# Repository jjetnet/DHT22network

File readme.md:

# DHT22network
wifi dht22 network

Note: there are many similar, and probably better implementation of
similar concepts. My python coding in particular is far from optimal
or elegant. This implementation has mobile notifications, plots and water partial pressure
calculations which distinguishes it from others, but if you don't need
this look around for better implementations.

## Overview:

Arduino code, eagle files and python script for a wifi based array of
humidity and temperature sensors sending data back periodically to a
server. The server generates plots and tables of current data
displayed on a webpage - on the local server, and/or on a remote web
server through ftp. The sensors are meant for indoors reading, with
outside temperature read from publicly available data from the
Australian bureau of meteorology (data for australia only...).  The
number of sensors is not really limited (Although past a certain
number i'm sure bugs will emerge), and the server just adapts when a
new sensor comes online.

Each sensor can be battery operated for a number of months or even
years depending on refresh settings and battery - power consumption
between readings is minimal. The server can send notificatinos to
android and iphone phones using the free pushetta service/app (See
www.pushetta.com) when outside temperature goes above or below user
defined thresholds - useful to remember to close windows, curtains or
blinds.  Each sensor also reads its battery level, also displayed on
the webpage as battery voltage with a crude red/green color coding
depending on battery state.

For example of what the webpage looks like see
webpageexample.png. Data displayed includes temperature, relative
humidity and the water partial pressure - the latter is absolute
rather than relative, and is more informative if you want to control
the flow of humidity between two rooms or between outdoows and
indoors: if two rooms are at different temperatures but identical
relative humidity, there will still be a net flow of water vapour from
the space with the higher partial water pressure to the room with the
lower one. If you want to keep humidity down indoors in summer, this
is the quantity to watch to close/open windows, rather than the
relative humidity.

Each sensor is based on an esp8266 - specifically i used a sparkfun
esp8266 thing, which includes a convenient LiPo battery charger. Wifi
network and key, location name, and python server addess and port have
to be adjusted in the arduino code before uploading.

The server collecting data is a python script, which has to be run
with sufficient priviledges to write onto the web server's folder (eg
`/var/www/` ). All server data is defined in a separate configuration
script (tempTCPconfig.py). I run mine on a raspbery pi.

## Hardware

A minimal version can be assembled without PCB, using a ESP8266 thing the DHT22 sensor, and a jumper wire between XPD and DTR (which needs to be removed for programming). To add battery monitoring, two resistors straight onto the ESP8266 thing between Vin, Gnd and Analog in forming a ~1/5 voltage divider is enough. (220k between Vin and Analog in, 56k between gnd and Analog in) (see eagle schematic for details).

Alternatively, a PCB can be used to clean up the circuit: 

The current version of the pcb (eagle file) is awkward - components are on
the copper side, which makes for some difficult soldering for some
pins.

The two jpeg files show an example of an assembled sensor module using PCB,
outside its casing - as mentioned it is a tad awkward in this
implementation. There's some hot glue that was requried to stabilise
some of the copper wiring which had lifted off when accidentally
pushing on the module... The top view with sensor rotated shows the
two resistors that make up the voltage divider to bring the battery
voltage within the range of the ESP8266 1V ADC, as well as the jumper
that needs to be removed for programming (it connects XPD to DTR to
enable deep sleep - see [sparkfun's sleepmode tutorial](https://learn.sparkfun.com/tutorials/esp8266-thing-hookup-guide/example-sketch-goodnight-thing-sleep-mode). The
six open pins are a copy of the programming port of the esp8266 so
that the the module can still be programmed.  This particular example
uses a DHT22 module from df robotics, but a naked DHT22 can also be
used.

For the battery to last months rather than hours or days, the power LED has to be disconnected, see [sparkfun's sleepmode tutorial](https://learn.sparkfun.com/tutorials/esp8266-thing-hookup-guide/example-sketch-goodnight-thing-sleep-mode)

For this example, I used a LiPo 1000mAh LiPo battery, which is of similar size to the esp8266 thing module.

## Installation:
The python-based server requires a number of libraries,
some of which are not in the default python install for raspberry
pi (if you chose to run the server on a raspberry pi). In particular pushetta, matplotlib and a recent version of numpy
are requried, which you may have to install from source depending on
your distribution/package manager. I'm not sure which version is
required, but it runs with numpy 1.11.0, matplotlib 1.1.1rc2, pushetta
1.0.15.
Notifications require a free account with the pushetta service. For this, and how to install the pushetta python package, see [the puhsetta help page](http://pushetta.com/pushetta-docs).
Feel free to contact me (open an issue) if you have any trouble installing or running the server.

## Updates:
### 13/08/16
* increased stability: exception handling for ftp and pushetta. The python server seems very stable now.
* remover redundant, unused plot routine.

### 30/07/16
* fixed stability issues when remote ftp server or bureau of meteorology websites are not responsive.
* fixed plotting - no more error messages when insufficient data points, and limited long-term plot to last 30 days for readability

## Known issues:
* Arduino code:  If the server is down or a sensor module fails for any other reason to communicate with the server, it will keep trying continuously for ever - the battery will then run out rapidly.
* safety: ftp passwords are in clear text in the python configuration file, and  so is the wifi password in the arduino code. MAke sure to protect those files. TCP communications between sensor module and server are unencrypted.

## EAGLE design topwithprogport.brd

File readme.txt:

# DHT22network
wifi dht22 network

Note: there are many similar, and probably better implementation of similar concepts. My python coding in particular is far from optimal or elegant. Look around for better implementations...

*** Overview: ***

Arduino code, eagle files and python script for a wifi based array of  humidity and temperature sensors sending data back periodcially to a server. The server generates plots and tables of current data displayed  on a webpage - on the local server, and/or on a remote web server through ftp. The sensors are meant for indoors reading, with outside temperature read from publicly available data from the Australian bureau of meteorology (data for australia only...).
The number of sensors is not really limited (Although past a certain number i'm sure bugs will emerge), and the server just adapts when a new sensor comes online. 

Each sensor can be battery operated for a number of months or even years depending on refresh settings and battery  - power consumption between readings is minimal. The server can send notificatinos to android and iphone phones using the free pushetta service/app (See www.pushetta.com) when outside temperature goes above or below user defined  thresholds - useful to remember to close windows, curtains or blinds.
Each sensor also reads its battery level, also displayed on the webpage as battery voltage with a crude red/green color coding depending on battery state.

For example of what the webpage looks like see webpageexample.png. Data displayed includes temperature, relative humidity and the water partial pressure - the latter is absolute rather than relative, and is more informative if you want to control the flow of humidity between two rooms or between outdoows and indoors: if two roowms are at different temperatures but identical relative humidity, there will still be a net flow of water vapour from the space with the higher partial water pressure to the room with the lower one. If you want to keep humidity down indoors in summer, this is the quantity to watch to close/open windows, rather than the relative humidity.

Each sensor is based on an esp8266 - specifically i used a sparkfun esp8266 thing, which includes a convenient LiPo battery charger. Wifi network and key,  location name, and python server addess and port have to be adjusted in the arduino code before uploading. 

The server collecting data is a python script, which has to be run with sufficient priviledges to write onto the web server's  folder (eg /var/www/ ). All server data is defined in a separate configuration script (tempTCPconfig.py). I run mine on a raspbery pi.

*** Hardware ***

The current version of eagle file's pcb is awkward - components are on the copper side, which makes for some difficult soldering for some pins. 

The two jpeg files show an example of an assembled sensor module, outside its casing - as mentioned it is a tad awkward in this implementation. There's some hot glue that was requried to stabilise some of the copper wiring which had lifted off when accidentally pushing on the module... The top view with sensor rotated shows the two resistors that make up the voltage divider to bring the battery voltage within the range of the ESP8266 1V ADC, as well as the jumper that needs to be removed for programming (it connects XPD to DTR to enable  deep sleep - see https://learn.sparkfun.com/tutorials/esp8266-thing-hookup-guide/example-sketch-goodnight-thing-sleep-mode). The six open pins are a copy of the programming port of the esp8266 so that the the module can still be programmed.
This particular example uses a DHT22 module from df robotics, but a naked DHT22 can also be used.

For the battery to last months rather than hours or days, the power LED has to be disconnected, see https://learn.sparkfun.com/tutorials/esp8266-thing-hookup-guide/example-sketch-goodnight-thing-sleep-mode

For this example, I used a LiPo 1000mAh LiPo battery, which is of similar size to the esp8266 thing module.

Known issues:
- Arduino code:  If the server is down or a sensor module fails for any other reason to communicate with the server, it will keep trying continuously for ever - the battery will then run out rapidly.
- Python code: the server is not bug free. It is stable for days to weeks at a time, but occasionally stops if communications with sensor module isn't quite as expected. I may now have fixed this bug - but i won't be sure for another few weeks...
- safety: ftp passwords are in clear text in the python configuration file, and  so is the wifi password in the arduino code. MAke sure to protect those files...

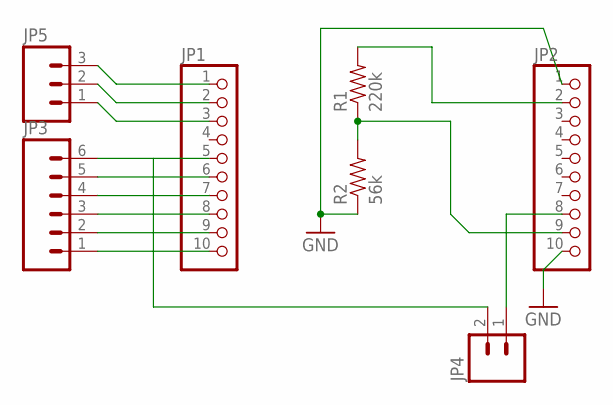
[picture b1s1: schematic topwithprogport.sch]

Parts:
JP1, JP2: PINHD-1X10; 1X10
JP3: M06LONGPADS; 1X06_LONGPADS
JP4: M02LOCK_LONGPADS; 1X02_LOCK_LONGPADS
JP5: M03LOCK_LONGPADS; 1X03_LOCK_LONGPADS
R1: 220k; AXIAL-0.4
R2: 56k; AXIAL-0.4

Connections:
GND: JP1.1, JP2.1, JP2.10, JP5.3, R2.P$1 (1)
unnamed: JP2.9, R1.P$1 (1), R2.P$2 (2)
unnamed: JP2.2, R1.P$2 (2)
unnamed: JP2.8, JP4.1
unnamed: JP1.5, JP3.6, JP4.2
unnamed: JP1.6, JP3.5
unnamed: JP1.7, JP3.4
unnamed: JP1.8, JP3.3
unnamed: JP1.9, JP3.2
unnamed: JP1.10, JP3.1
unnamed: JP1.2, JP5.2
unnamed: JP1.3, JP5.1

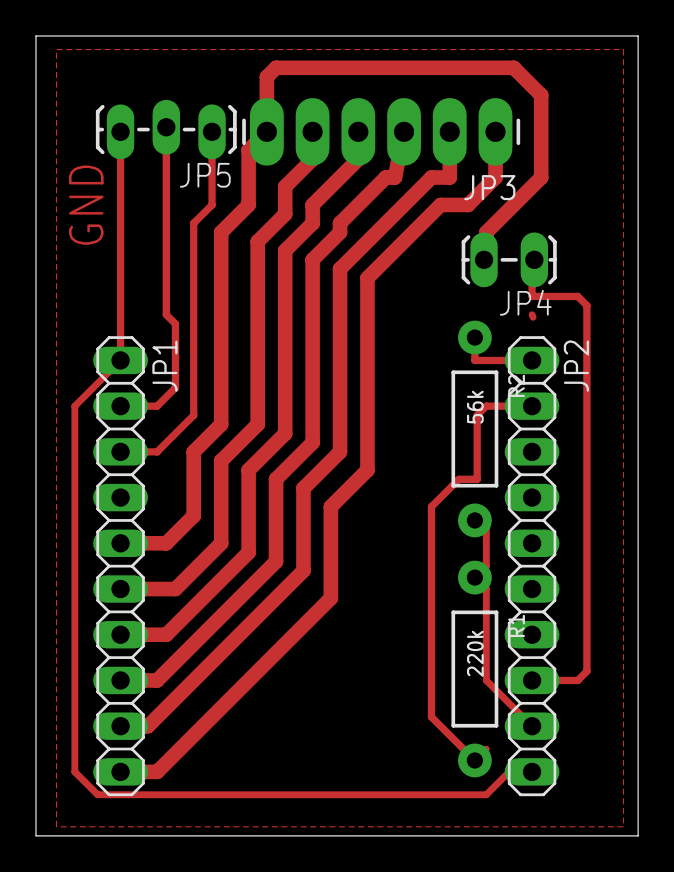
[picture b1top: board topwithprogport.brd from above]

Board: 2 copper layers, 33.5 x 44.4 mm, 7 parts (0 on the bottom side), 12 nets.

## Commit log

2016-07-09 :lollipop: Added .gitattributes & .gitignore files
2016-07-09 Initial release
    Mostly stable - see readme
2016-07-09 initial release with readme
    added readme file
2016-07-09 added pictures of sensor module
2016-07-09 added example of web page
2016-07-30 stability fixes
    * fixed stability issues when remote ftp server or bureau of meteorology
    websites are not responsive
    * fixed plotting - no more error messages when insufficient data points,
    and limited long-term plot to last 30 days for readability
2016-08-13 increased stability - added installation instructions
2017-10-07 streamlined error logging
    also changed to arduino folder structure
2017-10-07 fixed 'invalid value enountered bug' when date list contains NaN
2017-10-07 fixed error causing crash shortly after startup when only one data point available for day
    the server would crash after the first data is recieved if the server
    had been down for more than a day. This has now been fixed.
    Other bug fixes:
    - standard python error reporting is back
    - output files are flushed after writing to avoid delay in reportring
    - data is no longer duplicated in csv files
2018-07-29 changed urllib2 to requests
    BOM website was updated and did not respond to urllib2 requests without
    several additional headers - causing 403 errors in the previous version.
    Using requests library instead of urllib2 avoids this problem - and is
    easier.
    Also added checking that BOM data wasn't logged already for same time
    stamp to avoid duplication of data.
2018-09-15 now optionally publishes data to mqtt server , for compatibility with home assistant etc
    seems to work - to be confirmed in next few days.
    mqtt server is defined in config file
2018-09-16 added BOM to mqtt
    also publishes BOM data to mqtt (including water pressure) as
    DHTNetwork/BOM
2018-09-22 more frequent BOM data posts on mqtt
    BOM data posted on mqtt everytime sensor data recieved, makes debugging
    house assistant interface easier
2019-08-04 error handling for port scan
    added error handling for errors occuring from port scanning by home assistant
2019-08-04 updated readme to document mqtt

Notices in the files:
parts and their libraries:
SparkFun-Passives: Licensing: CC v3.0 Share-Alike You are welcome to use this library for commercial purposes.
SparkFun-Connectors: Licensing: Creative Commons ShareAlike 4.0 International - https://creativecommons.org/licenses/by-sa/4.0
